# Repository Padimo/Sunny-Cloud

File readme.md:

# Sunny Cloud
Sunny Cloud is an ESP32-based LED art decoration in the form of a cloud. It connects to the user's WiFi network to pull time and weather to determine the patterns the LEDs will follow. It will also run a web server where connecting to a url (likely esp.local) will allow the user to control the settings more precisely.

This specific Blueprint submission aims to make five clouds which will be linked to each other using ESPNow.

Moving forward, I would love to implement HomeKit or Matter support for this project, however it is not in the scope of this project currently.

Note that the bulk of this project is programming the ESP, not building the hardware.

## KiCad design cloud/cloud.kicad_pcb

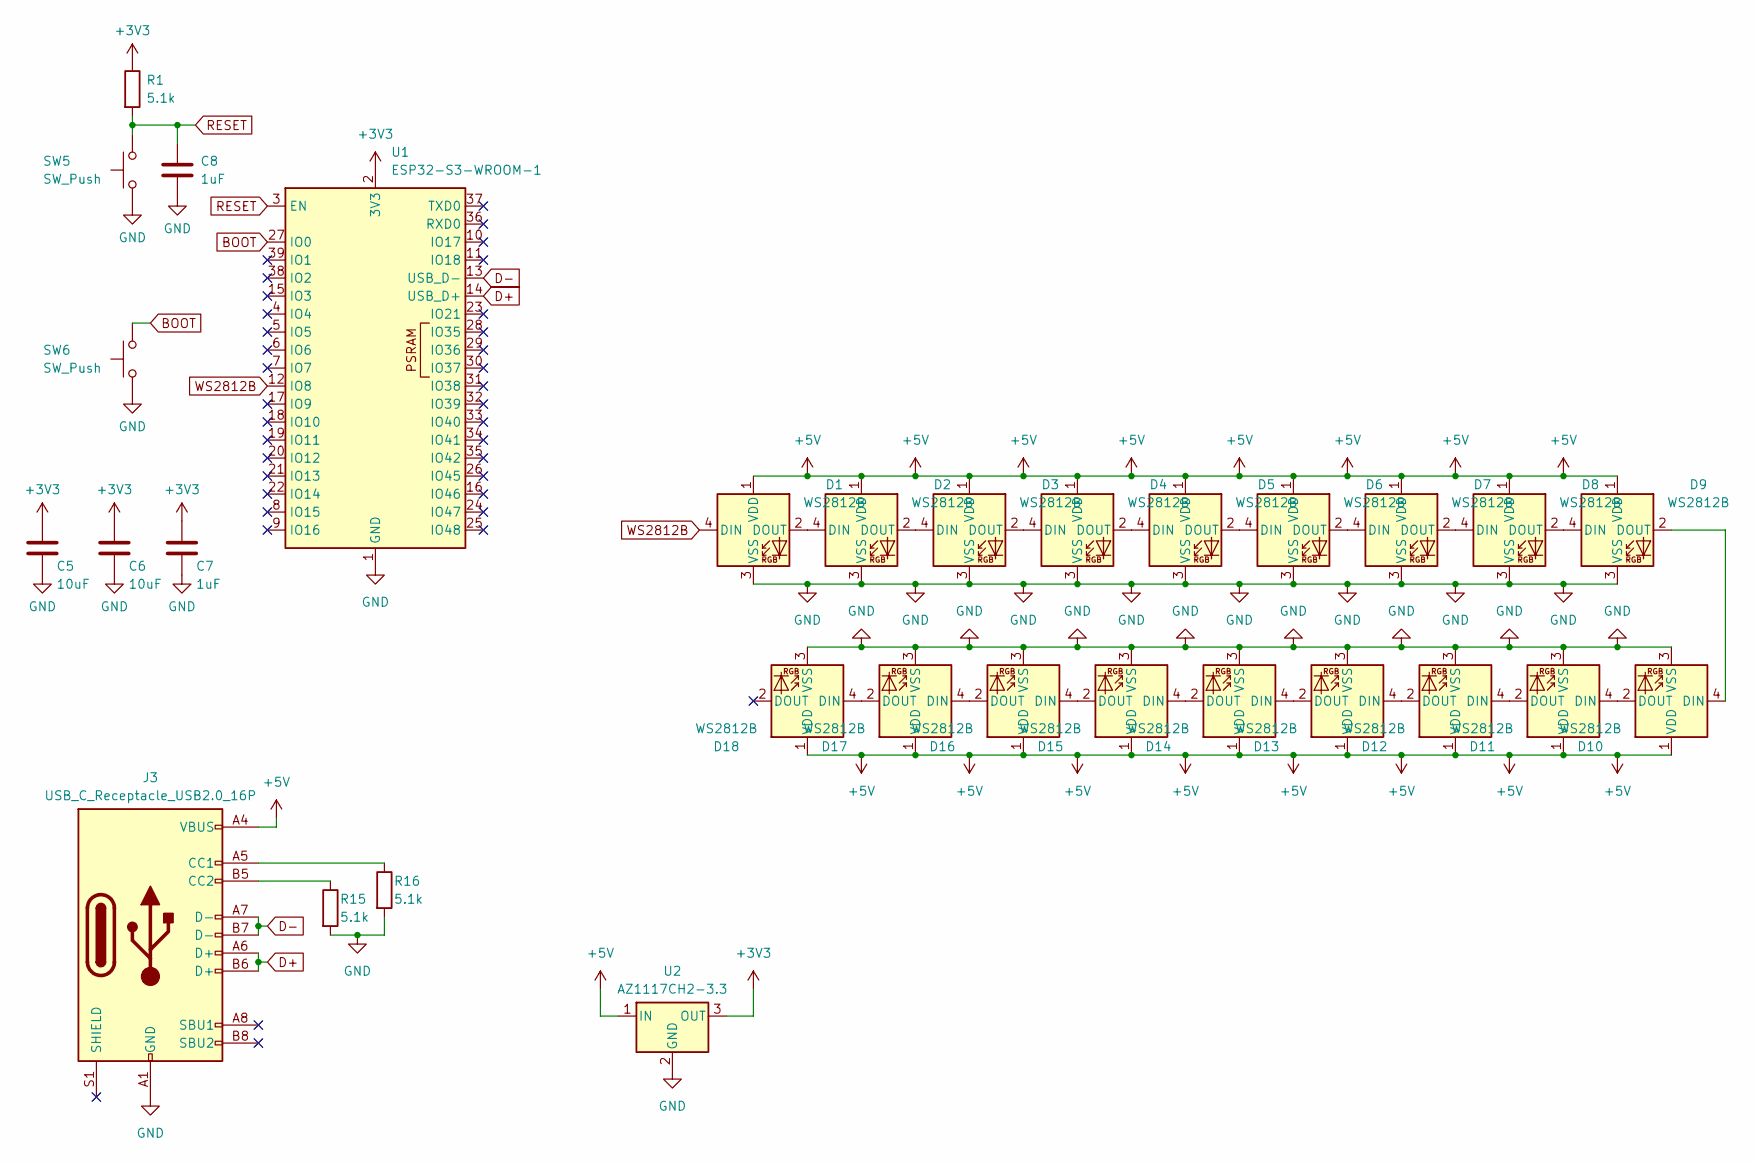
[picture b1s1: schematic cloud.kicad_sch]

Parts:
C5, C6: 10uF; C_0805_2012Metric
C7, C8: 1uF; C_0805_2012Metric
D1, D2, D3, D4, D5, D6, D7, D8, D9, D10, D11, D12, D13, D14, D15, D16, D17, D18: WS2812B; LED_WS2812B_PLCC4_5.0x5.0mm_P3.2mm
J3: USB_C_Receptacle_USB2.0_16P; USB_C_Receptacle_GCT_USB4085
R1, R15, R16: 5.1k; R_0805_2012Metric
SW5, SW6: SW_Push; SW_Push_1P1T_NO_CK_KSC6xxJ
U1: ESP32-S3-WROOM-1
U2: AZ1117CH2-3.3; SOT-223-3_TabPin2

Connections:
+3V3: C5.1, C6.1, C7.1, R1.1, U1.2 (3V3), U2.3 (OUT)
+5V: D1.1 (VDD), D2.1 (VDD), D3.1 (VDD), D4.1 (VDD), D5.1 (VDD), D6.1 (VDD), D7.1 (VDD), D8.1 (VDD), D9.1 (VDD), D10.1 (VDD), D11.1 (VDD), D12.1 (VDD), D13.1 (VDD), D14.1 (VDD), D15.1 (VDD), D16.1 (VDD), D17.1 (VDD), D18.1 (VDD), J3.A4 (VBUS), J3.A9 (VBUS), J3.B4 (VBUS), J3.B9 (VBUS), U2.1 (IN)
BOOT: SW6.2, U1.27 (IO0)
D+: J3.A6 (D+), J3.B6 (D+), U1.14 (USB_D+)
D-: J3.A7 (D-), J3.B7 (D-), U1.13 (USB_D-)
GND: C5.2, C6.2, C7.2, C8.2, D1.3 (VSS), D2.3 (VSS), D3.3 (VSS), D4.3 (VSS), D5.3 (VSS), D6.3 (VSS), D7.3 (VSS), D8.3 (VSS), D9.3 (VSS), D10.3 (VSS), D11.3 (VSS), D12.3 (VSS), D13.3 (VSS), D14.3 (VSS), D15.3 (VSS), D16.3 (VSS), D17.3 (VSS), D18.3 (VSS), J3.A1 (GND), J3.A12 (GND), J3.B1 (GND), J3.B12 (GND), R15.2, R16.2, SW5.1, SW6.1, U1.1 (GND), U1.40 (GND), U1.41 (GND), U2.2 (GND)
unnamed: D1.2 (DOUT), D2.4 (DIN)
unnamed: D2.2 (DOUT), D3.4 (DIN)
unnamed: D3.2 (DOUT), D4.4 (DIN)
unnamed: D4.2 (DOUT), D5.4 (DIN)
unnamed: D5.2 (DOUT), D6.4 (DIN)
unnamed: D6.2 (DOUT), D7.4 (DIN)
unnamed: D7.2 (DOUT), D8.4 (DIN)
unnamed: D8.2 (DOUT), D9.4 (DIN)
unnamed: D9.2 (DOUT), D10.4 (DIN)
unnamed: D10.2 (DOUT), D11.4 (DIN)
unnamed: D11.2 (DOUT), D12.4 (DIN)
unnamed: D12.2 (DOUT), D13.4 (DIN)
unnamed: D13.2 (DOUT), D14.4 (DIN)
unnamed: D14.2 (DOUT), D15.4 (DIN)
unnamed: D15.2 (DOUT), D16.4 (DIN)
unnamed: D16.2 (DOUT), D17.4 (DIN)
unnamed: D17.2 (DOUT), D18.4 (DIN)
unnamed: J3.A5 (CC1), R16.1
unnamed: J3.B5 (CC2), R15.1
RESET: C8.1, R1.2, SW5.2, U1.3 (EN)
WS2812B: D1.4 (DIN), U1.12 (IO8)

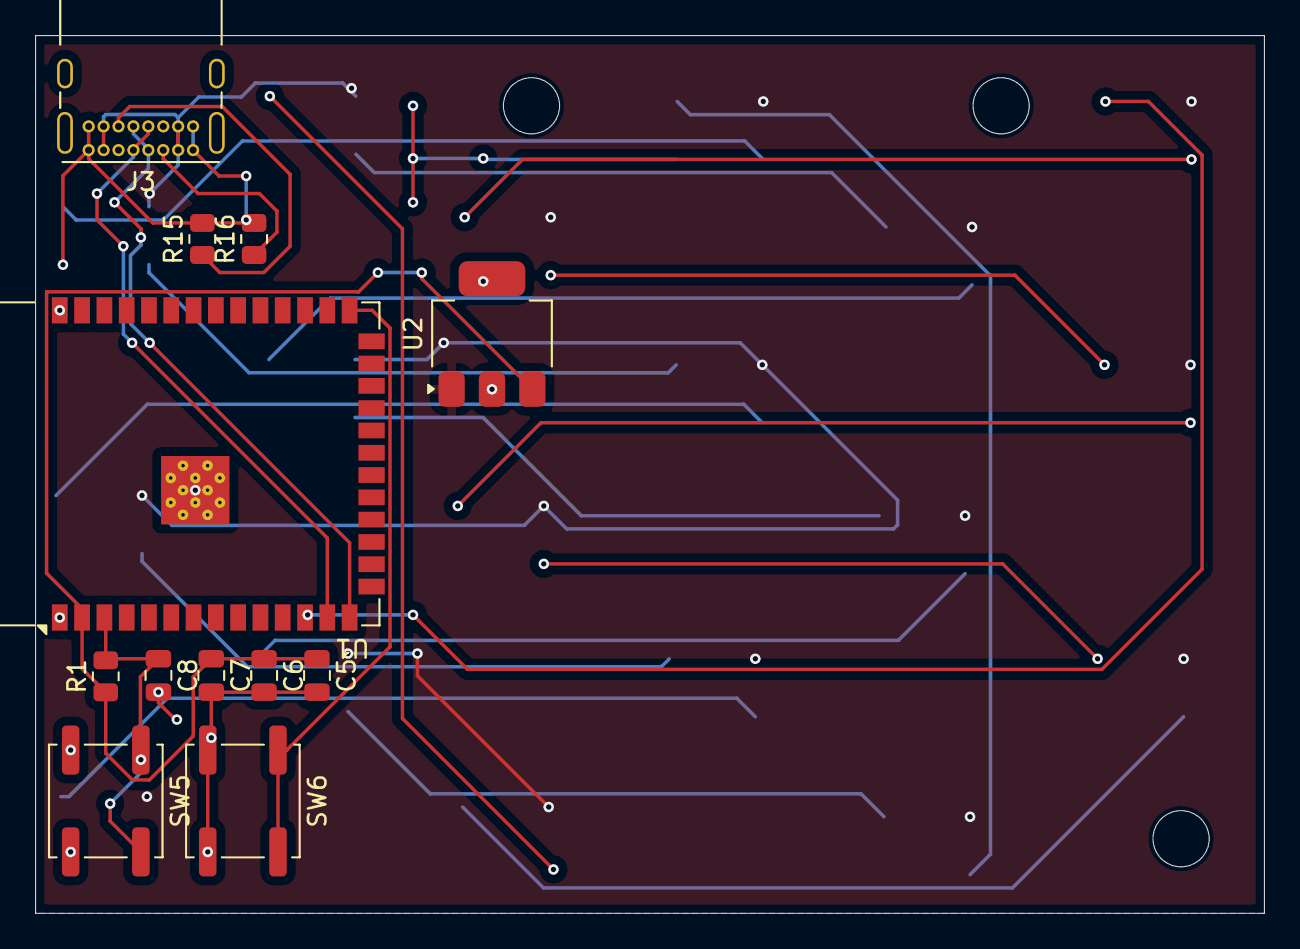
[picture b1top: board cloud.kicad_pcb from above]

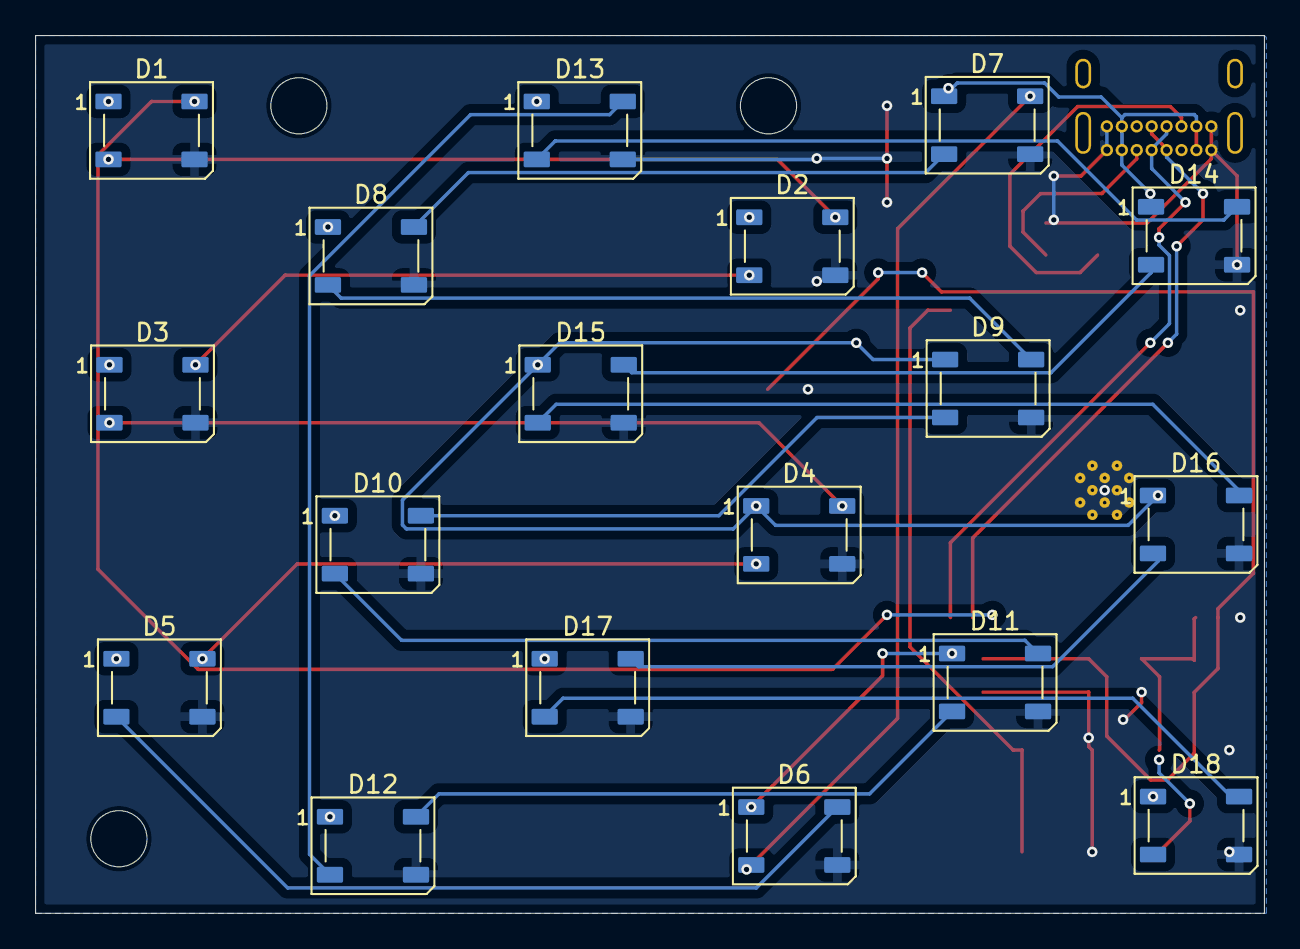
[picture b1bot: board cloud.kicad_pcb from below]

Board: 2 copper layers, 70.0 x 50.0 mm, 30 parts (18 on the bottom side), 27 nets.

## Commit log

2025-12-13 full pcb v1
2025-12-13 readme + images
2025-12-13 fix readme
2025-12-18 full assembly
2025-12-18 readme with images
2025-12-22 update pcb
